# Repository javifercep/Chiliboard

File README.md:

# Chiliboard
The Chiliboard is an Arduino form factor board with two CAN - 2.0B interfaces. It is based on STM32F105 MCU and can work as an extension of the [Noodleboard](https://github.com/javifercep/Noodleboard). It has been developed for the [MuBA](http://javisfryingchips.com/portfolio/detail/multi-bus-analyzer/) project.

##Features

 * STM32F105RGT6 microcontroller featuring 32-bit ARM Cortex-M3 core,256 KB Flash, 64 KB RAM in an LQFP64 package
 * Extension header fully compatible with Arduino™ form-factor
 * SN65HVD232: CAN transceiver
 * Board power supply: through pin 5 V (Arduino form-factor).
 * Four green user LEDs
 * Reset button
 * Headers for programming and debugging through SWD protocol

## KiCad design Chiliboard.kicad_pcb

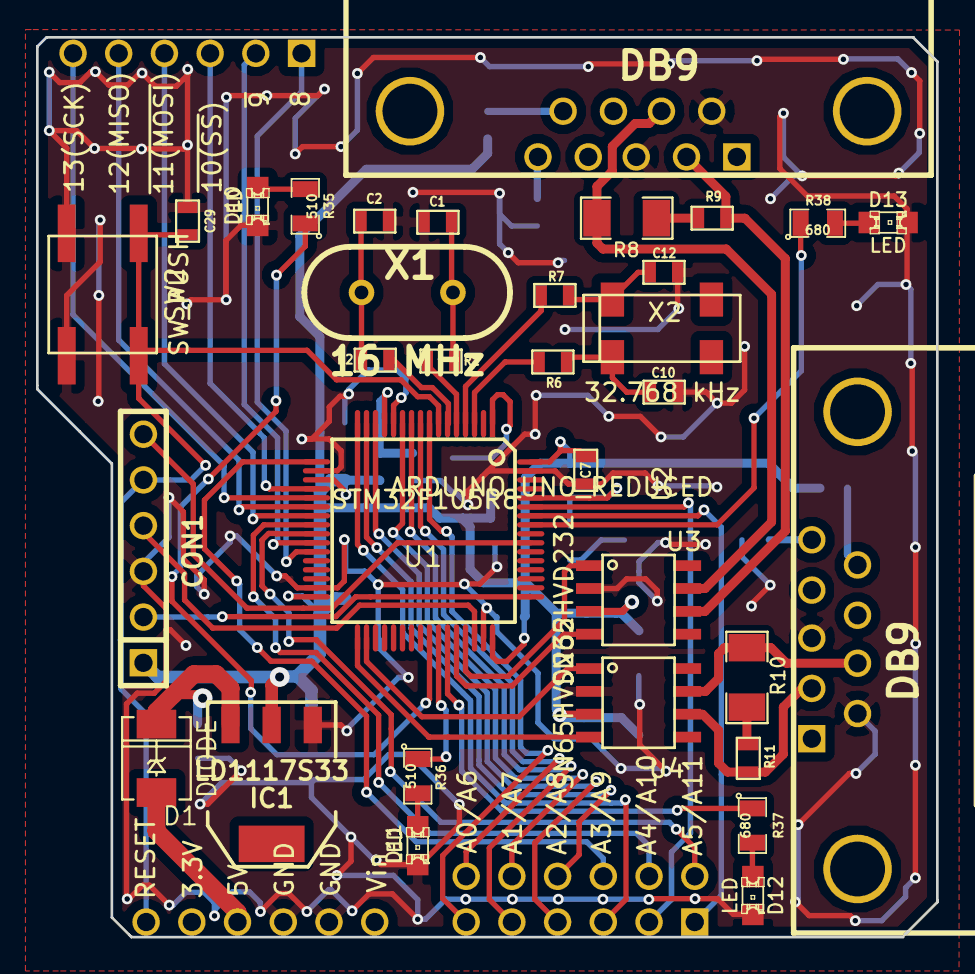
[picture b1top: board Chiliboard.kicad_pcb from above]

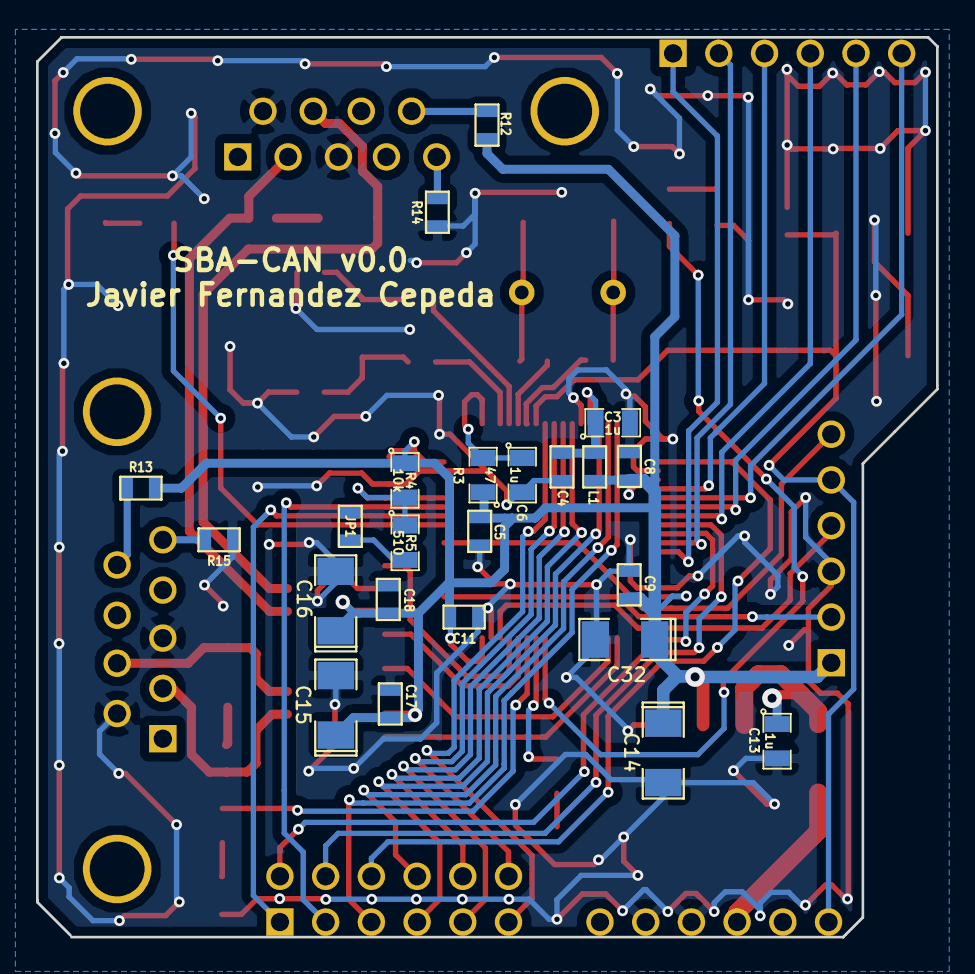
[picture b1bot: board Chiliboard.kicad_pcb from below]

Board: 2 copper layers, 50.0 x 50.0 mm, 57 parts (23 on the bottom side), 60 nets.

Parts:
C1, C2: 4.7p; SM0603
C3, C6, C13: 1u; SM0805
C4, C5, C7, C8, C9, C11, C17, C18, C29: 100n; SM0603
C10, C12: 6.8p; SM0603
C14, C15, C16: 10u; SM1206POL
C32: 4u7; SM1206POL
CON1: SWD; PIN_ARRAY-6X1
D1: DIODE; DO-214AC(SMA)
D10, D11, D12, D13: LED; LED-0805
IC1: LD1117S33; SOT223
J1, J2: DB9; DB9MC
JP1: JUMPER; SM0603
L1: fcm1608; SM0603
R1, R2, R6, R7, R9, R11, R12, R13, R14, R15: 0; SM0603
R3: 47; SM0805
R4: 10k; SM0805
R5, R35, R36: 510; SM0805
R8, R10: 120; SM1206
R37, R38: 680; SM0805
SW2: SW_PUSH; EVQP0
U1: STM32F105R8; LQFP64
U2: ARDUINO_UNO_REDUCED; ArduinoUNOShieldReduced
U3, U4: SN65HVD232; SOIC8
X1: 16 MHz; HC-49V
X2: 32.768 kHz; RTC

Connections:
/BOOT0: R4.2, R5.1, U1.60
/CAN Interface/3V3: C5.1, C7.2, C8.2, C9.2, C11.2, C14.1, C15.1, C16.1, C17.1, C18.1, C32.1, CON1.1, IC1.2, L1.1, R3.1, R4.1, R12.1, R13.1, U1.19, U1.32, U1.48, U1.64, U3.3, U4.3
/CAN Interface/CAN1_RX: U1.44, U3.4
/CAN Interface/CAN1_TX: U1.45, U3.1
/CAN Interface/CAN2_RX: U1.33, U4.4
/CAN Interface/CAN2_TX: U1.34, U4.1
/OSC32_IN: R6.2, U1.3
/OSC32_OUT: R7.2, U1.4
/OSC_IN: R1.2, U1.5
/OSC_OUT: R2.2, U1.6
/Peripherals/5V: D1.1, U2.22
/Peripherals/A0: U1.8, U2.19
/Peripherals/A1: U1.10, U2.18
/Peripherals/A2: U1.14, U2.17
/Peripherals/A3: U1.16, U2.16
/Peripherals/A6: U1.9, U2.26
/Peripherals/A7: U1.11, U2.27
/Peripherals/A8: U1.15, U2.28
/Peripherals/A9: U1.17, U2.29
/Peripherals/A10: U1.24, U2.30
/Peripherals/A11: U1.25, U2.31
/Peripherals/GPIO1: U1.27, U2.8
/Peripherals/LED1: R35.1, U1.41
/Peripherals/LED2: R36.1, U1.42
/Peripherals/LED3: R37.1, U1.43
/Peripherals/LED4: R38.1, U1.57
/Peripherals/PWM1: U1.26, U2.9
/Peripherals/RESET_BUTTON: C29.1, CON1.5, SW2.1, U1.7, U2.24
/Peripherals/SCL: U1.58, U2.14
/Peripherals/SDA: U1.59, U2.15
/Peripherals/SPI_MISO: U1.22, U2.12
/Peripherals/SPI_MOSI: U1.23, U2.11
/Peripherals/SPI_NSS: U1.20, U2.10
/Peripherals/SPI_SCLK: U1.21, U2.13
/SWCLK: CON1.2, U1.49
/SWDIO: CON1.4, U1.46
/SWO: CON1.6, U1.55
/VBAT: C6.1, R3.2, U1.1
/VDDA: C3.1, C4.1, L1.2, U1.13
GND: C1.1, C2.1, C3.2, C4.2, C5.2, C6.2, C7.1, C8.1, C9.1, C10.1, C11.1, C12.1, C13.2, C14.2, C15.2, C16.2, C17.2, C18.2, C29.2, C32.2, CON1.3, D10.2, D11.2, D12.2, D13.2, IC1.1, J1.3, J1.6, J2.3, J2.6, JP1.2, R14.1, R15.1, SW2.2, U1.12, U1.18, U1.31, U1.47, U1.63, U2.21, U2.25, U3.2, U4.2
unnamed: C10.2, R6.1, X2.2
unnamed: C12.2, R7.1, X2.1
unnamed: JP1.1, R5.2
unnamed: C1.2, R1.1, X1.2
unnamed: C2.2, R2.1, X1.1
unnamed: C13.1, D1.2, IC1.3
unnamed: D10.1, R35.2
unnamed: D11.1, R36.2
unnamed: D13.1, R38.2
unnamed: D12.1, R37.2
unnamed: R10.2, R11.1
unnamed: J1.2, R9.2, U3.6
unnamed: J1.7, R8.1, U3.7
unnamed: J2.5, R15.2
unnamed: J2.9, R13.2
unnamed: J1.9, R12.2
unnamed: J1.5, R14.2
unnamed: J2.7, R10.1, U4.7
unnamed: R8.2, R9.1
unnamed: J2.2, R11.2, U4.6

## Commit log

2015-05-23 - Added license and gitignore file - Updated README file
2015-05-23 Added initial design
